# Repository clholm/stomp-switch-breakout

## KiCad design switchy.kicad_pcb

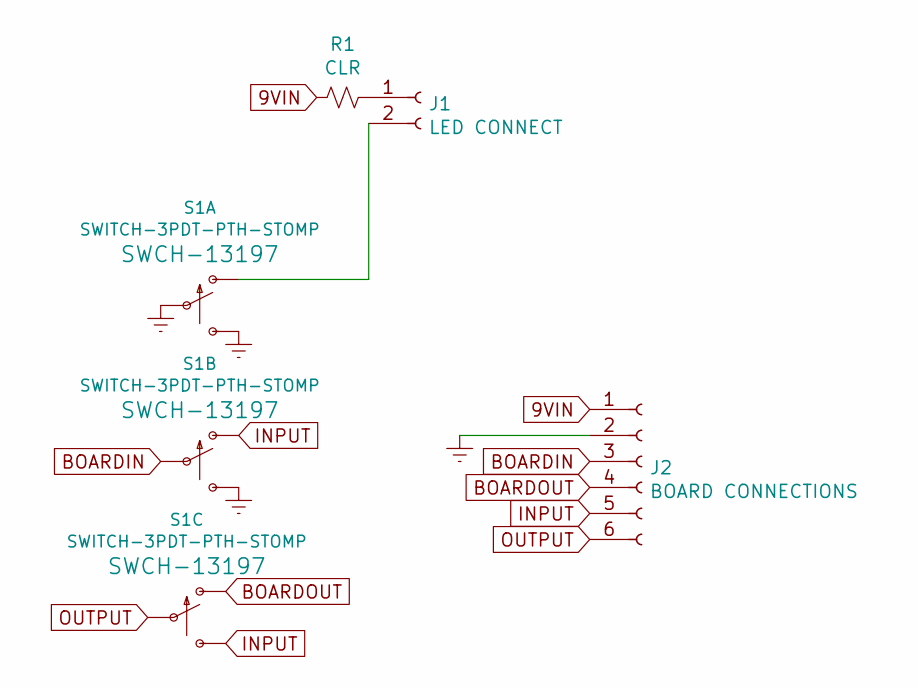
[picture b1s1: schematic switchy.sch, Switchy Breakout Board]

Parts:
J1: LED CONNECT; PinHeader_1x02_P2.54mm_Vertical
J2: BOARD CONNECTIONS; PinHeader_1x06_P2.54mm_Vertical
R1: CLR; 0.3_resistor
S1: SWITCH-3PDT-PTH-STOMP; STOMP_SWITCH_3PDT_TAIWAY_LOW_PROFILE

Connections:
9VIN: J2.1, R1.2
BOARDIN: J2.3, S1.P$5
BOARDOUT: J2.4, S1.P$7 (O)
Earth: J2.2, S1.P$2, S1.P$3 (S), S1.P$6 (S)
INPUT: J2.5, S1.P$4 (O), S1.P$9 (S)
unnamed: J1.1, R1.1
unnamed: J1.2, S1.P$1 (O)
OUTPUT: J2.6, S1.P$8

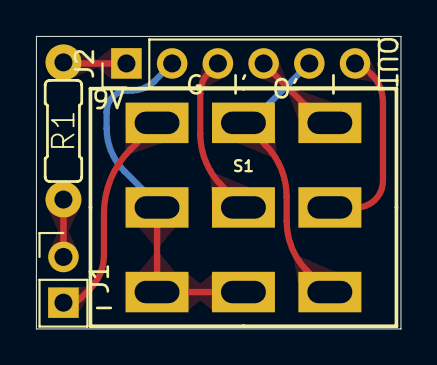
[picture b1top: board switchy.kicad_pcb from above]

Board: 2 copper layers, 20.2 x 16.2 mm, 4 parts (0 on the bottom side), 8 nets.

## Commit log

2022-03-26 3PDT breakout
2023-07-27 update with kicad 7, improved silkscreen labels
2023-07-27 updated manufacturing files
2023-07-27 removed old mfg artifacts
